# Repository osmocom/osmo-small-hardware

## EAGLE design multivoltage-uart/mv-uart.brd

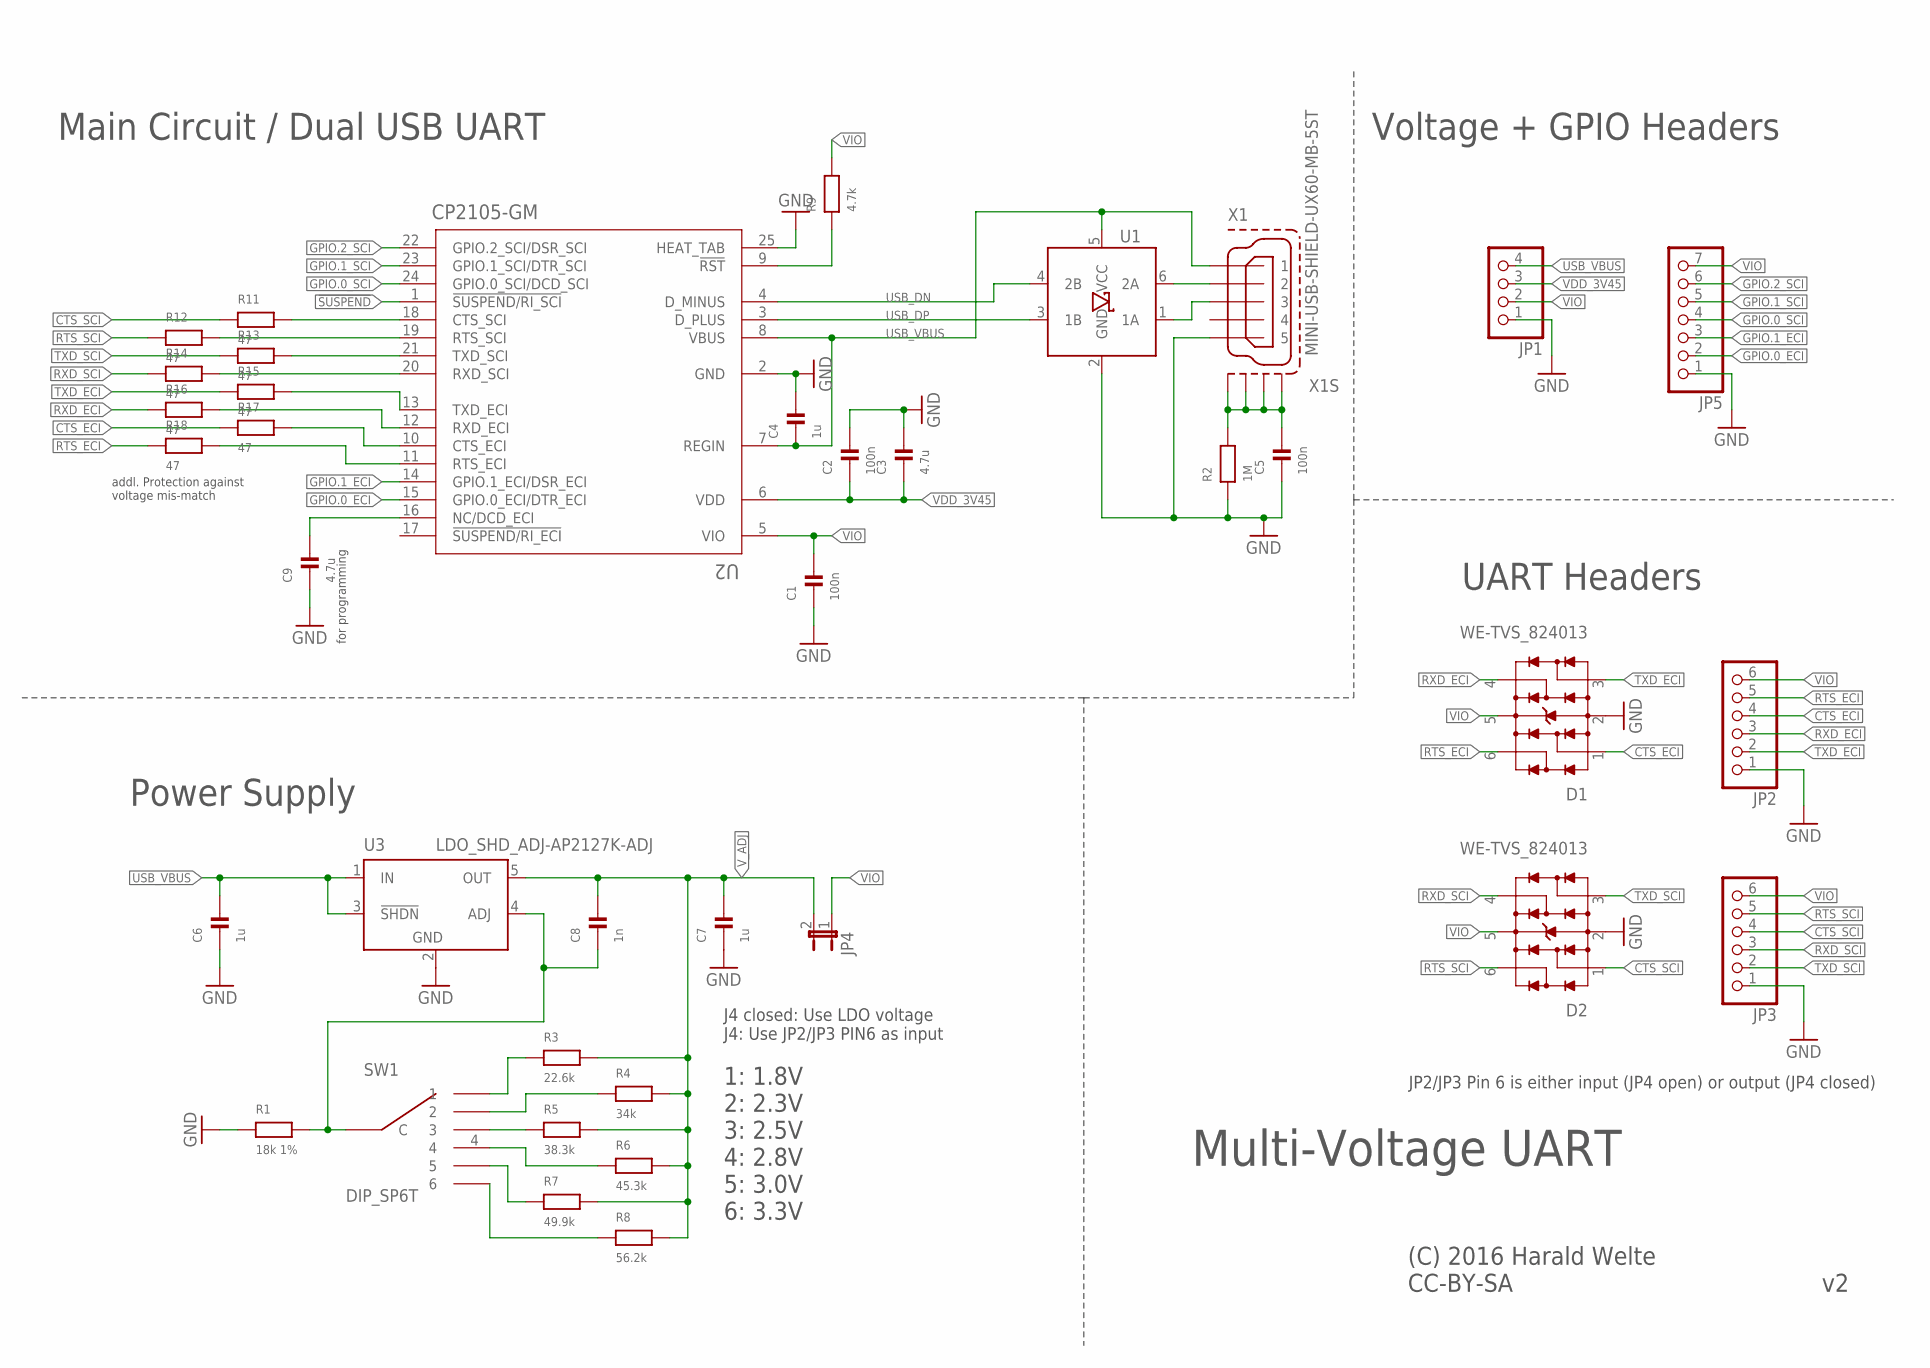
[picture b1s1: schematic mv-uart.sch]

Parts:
C1, C2, C5: 100n; _0603; MANUFACTURERPARTNUMBER GRM033R61C104KE84D
C3, C9: 4.7u; _0603; MANUFACTURERPARTNUMBER CL10A475KP8NNNC
C4, C6, C7: 1u; _0603; MANUFACTURERPARTNUMBER GRM188R61C105KA93J
C8: 1n; _0603; MANUFACTURERPARTNUMBER CL10B102KC8NNNC
D1, D2: WE-TVS_824013; WE-TVS_SOT23-6L; MANUFACTURERPARTNUMBER 824013
JP1: PINHD-1X4; 1X04; MANUFACTURERPARTNUMBER M20-9990445
JP2, JP3: PINHD-1X6/90; 1X06/90; MANUFACTURERPARTNUMBER M20-9960645
JP4: JP1E; JP1; MANUFACTURERPARTNUMBER UNKNOWN MANUFACTURER PART NUMBER
JP5: PINHD-1X7; 1X07; MANUFACTURERPARTNUMBER PRPC007SAAN-RC
R1: 18k 1%; _0603; MANUFACTURERPARTNUMBER RC0603FR-0718KL
R2: 1M; _0603; MANUFACTURERPARTNUMBER RC0603J105CS
R3: 22.6k; _0603; MANUFACTURERPARTNUMBER RC0603FR-0722K6L
R4: 34k; _0603; MANUFACTURERPARTNUMBER RC0603FR-0734KL
R5: 38.3k; _0603; MANUFACTURERPARTNUMBER RC0603FR-0738K3L
R6: 45.3k; _0603; MANUFACTURERPARTNUMBER RC0603FR-0745K3L
R7: 49.9k; _0603; MANUFACTURERPARTNUMBER RC0603FR-0749K9L
R8: 56.2k; _0603; MANUFACTURERPARTNUMBER RC0603FR-0756K2L
R9: 4.7k; _0603; MANUFACTURERPARTNUMBER RC0603JR-074K7L
R11, R12, R13, R14, R15, R16, R17, R18: 47; _0603; MANUFACTURERPARTNUMBER RC0603JR-0747RL
SW1: DIP_SP6T; MANUFACTURERPARTNUMBER SS-10-16SP-L-AE
U1: IP4234CZ6; TSOP-6; MANUFACTURERPARTNUMBER IP4234CZ6,125
U2: CP2105-GM; QFN24_4X4; MANUFACTURERPARTNUMBER CP2105-F01-GM
U3: LDO_SHD_ADJ-AP2127K-ADJ; SOT23L; MANUFACTURERPARTNUMBER AP2127K-ADJTRG1
X1: MINI-USB-SHIELD-UX60-MB-5ST; UX60-MB-5ST; MANUFACTURERPARTNUMBER UX60-MB-5ST

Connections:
!SUSPEND: U2.1 (!SUSPEND/RI_SCI)
CTS_ECI: D1.1, JP2.4, R17.1
CTS_SCI: D2.1, JP3.4, R11.1
GND: C1.1, C2.2, C3.2, C4.2, C5.1, C6.1, C7.1, C9.1, D1.2 (GND), D2.2 (GND), JP1.1, JP2.1, JP3.1, JP5.1, R1.1, R2.1, U1.2 (GND), U2.2 (GND), U2.25 (HEAT_TAB), U3.2 (GND), X1.5
GPIO.0_ECI: JP5.2, U2.15 (GPIO.0_ECI/DTR_ECI)
GPIO.0_SCI: JP5.4, U2.24 (GPIO.0_SCI/DCD_SCI)
GPIO.1_ECI: JP5.3, U2.14 (GPIO.1_ECI/DSR_ECI)
GPIO.1_SCI: JP5.5, U2.23 (GPIO.1_SCI/DTR_SCI)
GPIO.2_SCI: JP5.6, U2.22 (GPIO.2_SCI/DSR_SCI)
unnamed: R3.1, SW1.1
unnamed: R4.1, SW1.2
unnamed: R5.1, SW1.3
unnamed: R6.1, SW1.4
unnamed: C5.2, R2.2, X1.M1 (S1), X1.M2 (S2), X1.M3 (S3), X1.M4 (S4)
unnamed: R7.1, SW1.5
unnamed: R8.1, SW1.6
unnamed: R9.1, U2.9 (!RST)
unnamed: C9.2, U2.16 (NC/DCD_ECI)
unnamed: R11.2, U2.18 (CTS_SCI)
unnamed: R12.2, U2.19 (RTS_SCI)
unnamed: R13.2, U2.21 (TXD_SCI)
unnamed: R14.2, U2.20 (RXD_SCI)
unnamed: R15.2, U2.13 (TXD_ECI)
unnamed: C8.1, R1.2, SW1.C, U3.4 (ADJ)
unnamed: R16.2, U2.12 (RXD_ECI)
unnamed: R17.2, U2.10 (CTS_ECI)
unnamed: R18.2, U2.11 (RTS_ECI)
RTS_ECI: D1.6 (4), JP2.5, R18.1
RTS_SCI: D2.6 (4), JP3.5, R12.1
RXD_ECI: D1.4 (3), JP2.3, R16.1
RXD_SCI: D2.4 (3), JP3.3, R14.1
TXD_ECI: D1.3 (2), JP2.2, R15.1
TXD_SCI: D2.3 (2), JP3.2, R13.1
USB_DN: U1.4 (2B), U2.4 (D_MINUS)
USB_DP: U1.3 (1B), U2.3 (D_PLUS)
USB_VBUS: C4.1, C6.2, JP1.4, U1.5 (VCC), U2.7 (REGIN), U2.8 (VBUS), U3.1 (IN), U3.3 (!SHDN), X1.1
VDD_3V45: C2.1, C3.1, JP1.3, U2.6 (VDD)
VIO: C1.2, D1.5 (VDD), D2.5 (VDD), JP1.2, JP2.6, JP3.6, JP4.1, JP5.7, R9.2, U2.5 (VIO)
V_ADJ: C7.2, C8.2, JP4.2, R3.2, R4.2, R5.2, R6.2, R7.2, R8.2, U3.5 (OUT)
_USB_DN: U1.6 (2A), X1.2
_USB_DP: U1.1 (1A), X1.3

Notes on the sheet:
Main Circuit / Dual USB UART
Power Supply
Voltage + GPIO Headers
UART Headers
Multi-Voltage UART
(C) 2016 Harald Welte CC-BY-SA
J4 closed: Use LDO voltage J4: Use JP2/JP3 PIN6 as input
JP2/JP3 Pin 6 is either input (JP4 open) or output (JP4 closed)
addl. Protection against voltage mis-match
for programming
1: 1.8V 2: 2.3V 3: 2.5V 4: 2.8V 5: 3.0V 6: 3.3V

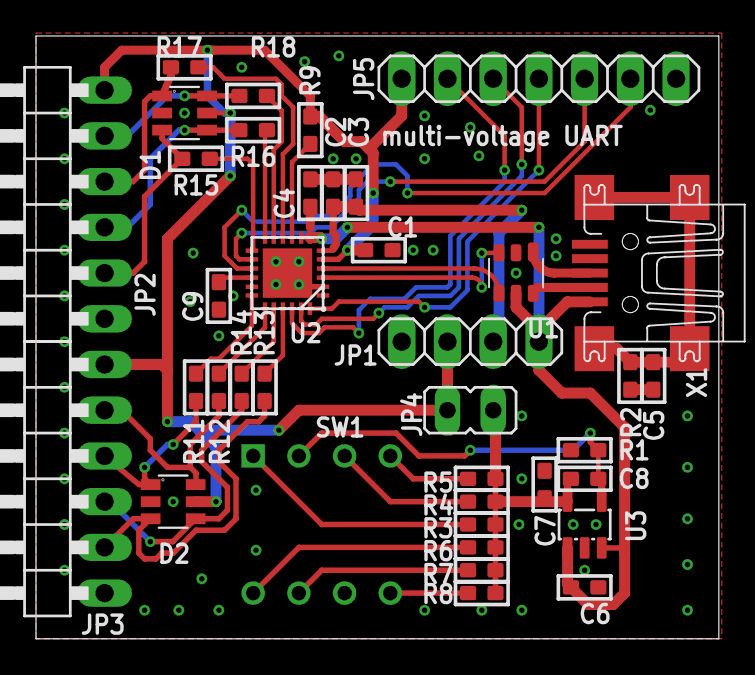
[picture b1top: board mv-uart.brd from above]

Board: 2 copper layers, 37.9 x 33.5 mm, 38 parts (0 on the bottom side), 40 nets.

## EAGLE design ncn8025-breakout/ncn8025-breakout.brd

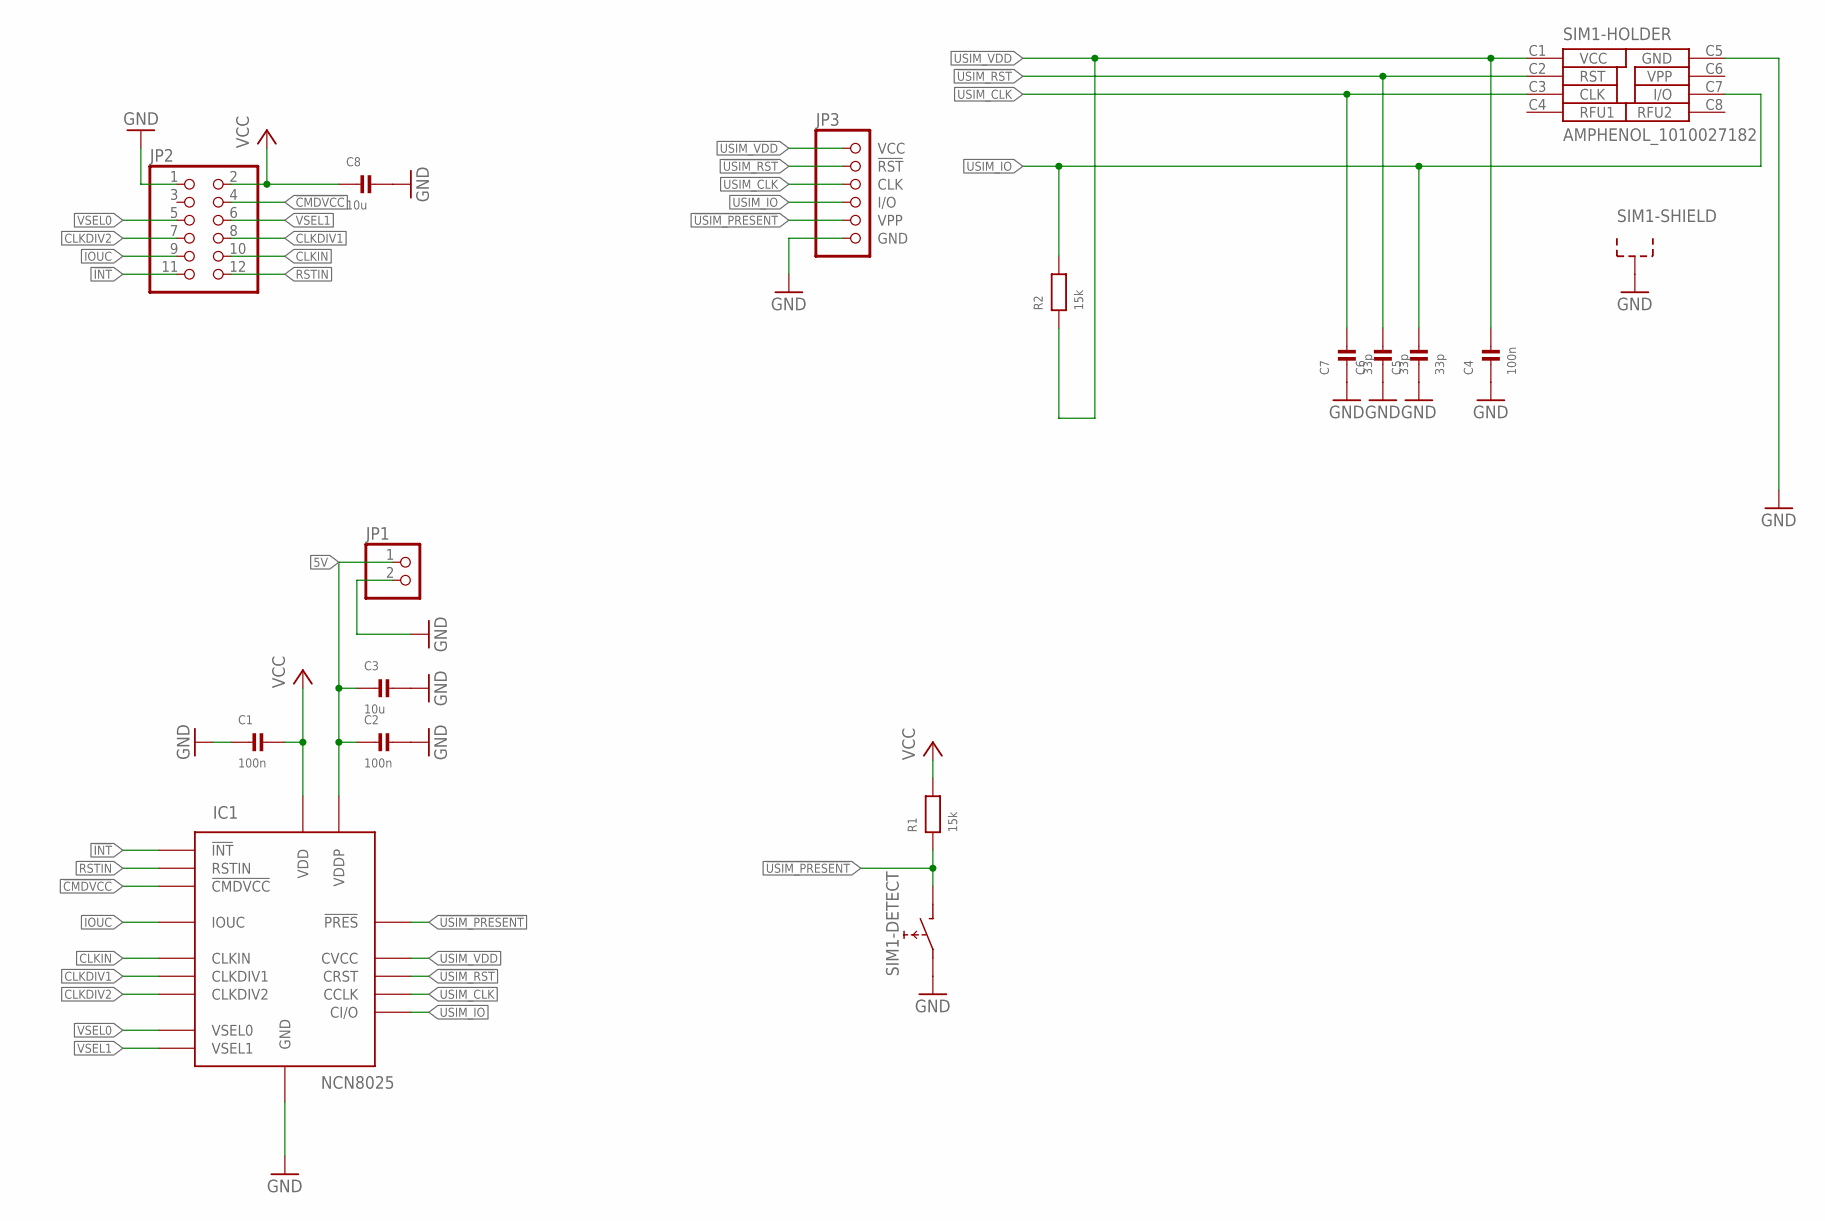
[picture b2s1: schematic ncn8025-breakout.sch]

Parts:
C1, C2, C4: 100n; _0603
C3, C8: 10u; _0603
C5, C6, C7: 33p; _0603
IC1: NCN8025; QFN16_3X3
JP1: PINHD-1X2; 1X02
JP2: PINHD-2X6; 2X06
JP3: PINHD-1X6; 1X06
R1, R2: 15k; _0603
SIM1: AMPHENOL_1010027182; SIM-AMPHENOL

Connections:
5V: C2.1, C3.1, IC1.2 (VDDP), JP1.1
!CMDVCC: IC1.8 (!CMDVCC), JP2.4
!INT: IC1.11 (!INT), JP2.11
!USIM_PRESENT: IC1.3 (!PRES), JP3.5 (VPP), R1.1, SIM1.SW2 (1)
!USIM_RST: C6.2, IC1.6 (CRST), JP3.2 (!RST), SIM1.C2 (RST)
CLKDIV1: IC1.14 (CLKDIV1), JP2.8
CLKDIV2: IC1.15 (CLKDIV2), JP2.7
CLKIN: IC1.12 (CLKIN), JP2.10
GND: C1.1, C2.2, C3.2, C4.1, C5.1, C6.1, C7.1, C8.2, IC1.EXPPAD (GND), JP1.2, JP2.1, JP3.6 (GND), SIM1.@2 (SHLD), SIM1.@3 (SHLD), SIM1.C5 (GND), SIM1.SW1 (0)
IOUC: IC1.13 (IOUC), JP2.9
RSTIN: IC1.9 (RSTIN), JP2.12
USIM_CLK: C7.2, IC1.5 (CCLK), JP3.3 (CLK), SIM1.C3 (CLK)
USIM_IO: C5.2, IC1.4 (CI/O), JP3.4 (I/O), R2.2, SIM1.C7 (I/O)
USIM_VDD: C4.2, IC1.7 (CVCC), JP3.1 (VCC), R2.1, SIM1.C1 (VCC)
VCC: C1.2, C8.1, IC1.10 (VDD), JP2.2, R1.2
VPP: SIM1.C6 (VPP)
VSEL0: IC1.1 (VSEL0), JP2.5
VSEL1: IC1.16 (VSEL1), JP2.6

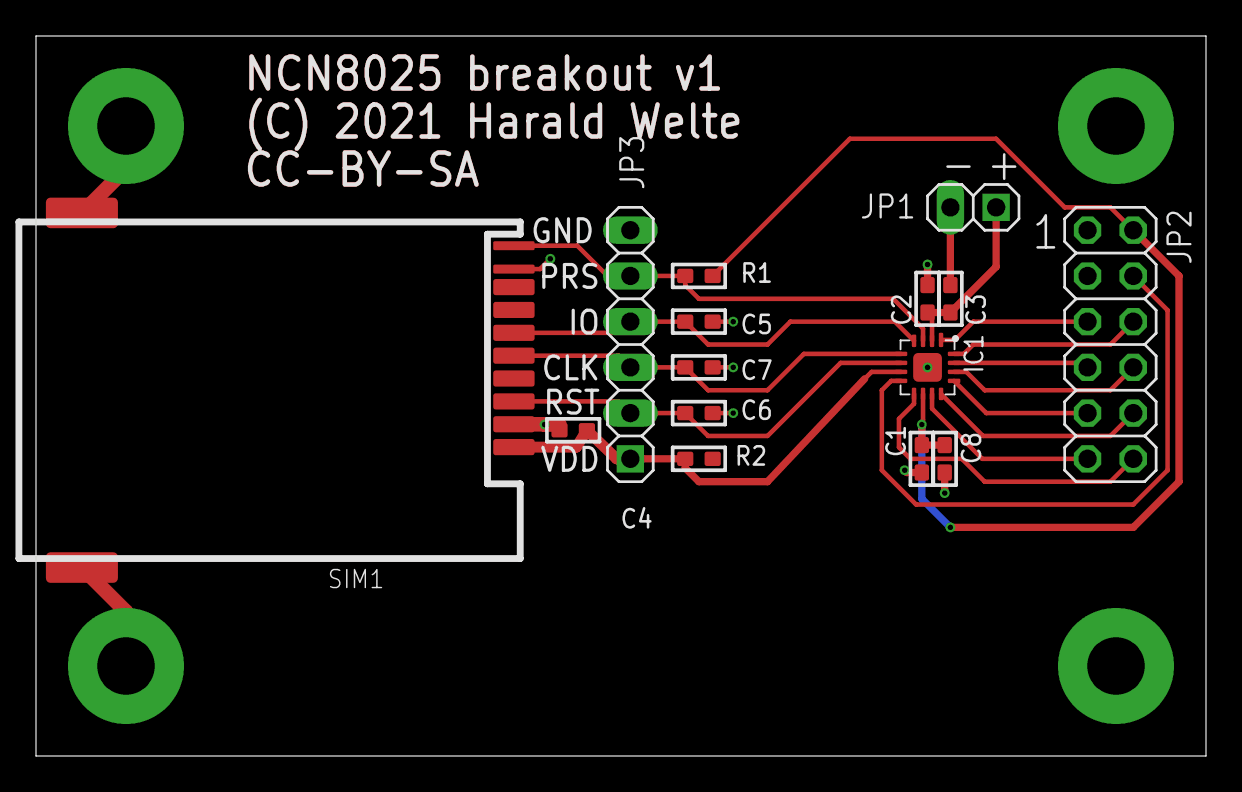
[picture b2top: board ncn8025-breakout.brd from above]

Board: 2 copper layers, 65.0 x 40.0 mm, 15 parts (0 on the bottom side), 17 nets.

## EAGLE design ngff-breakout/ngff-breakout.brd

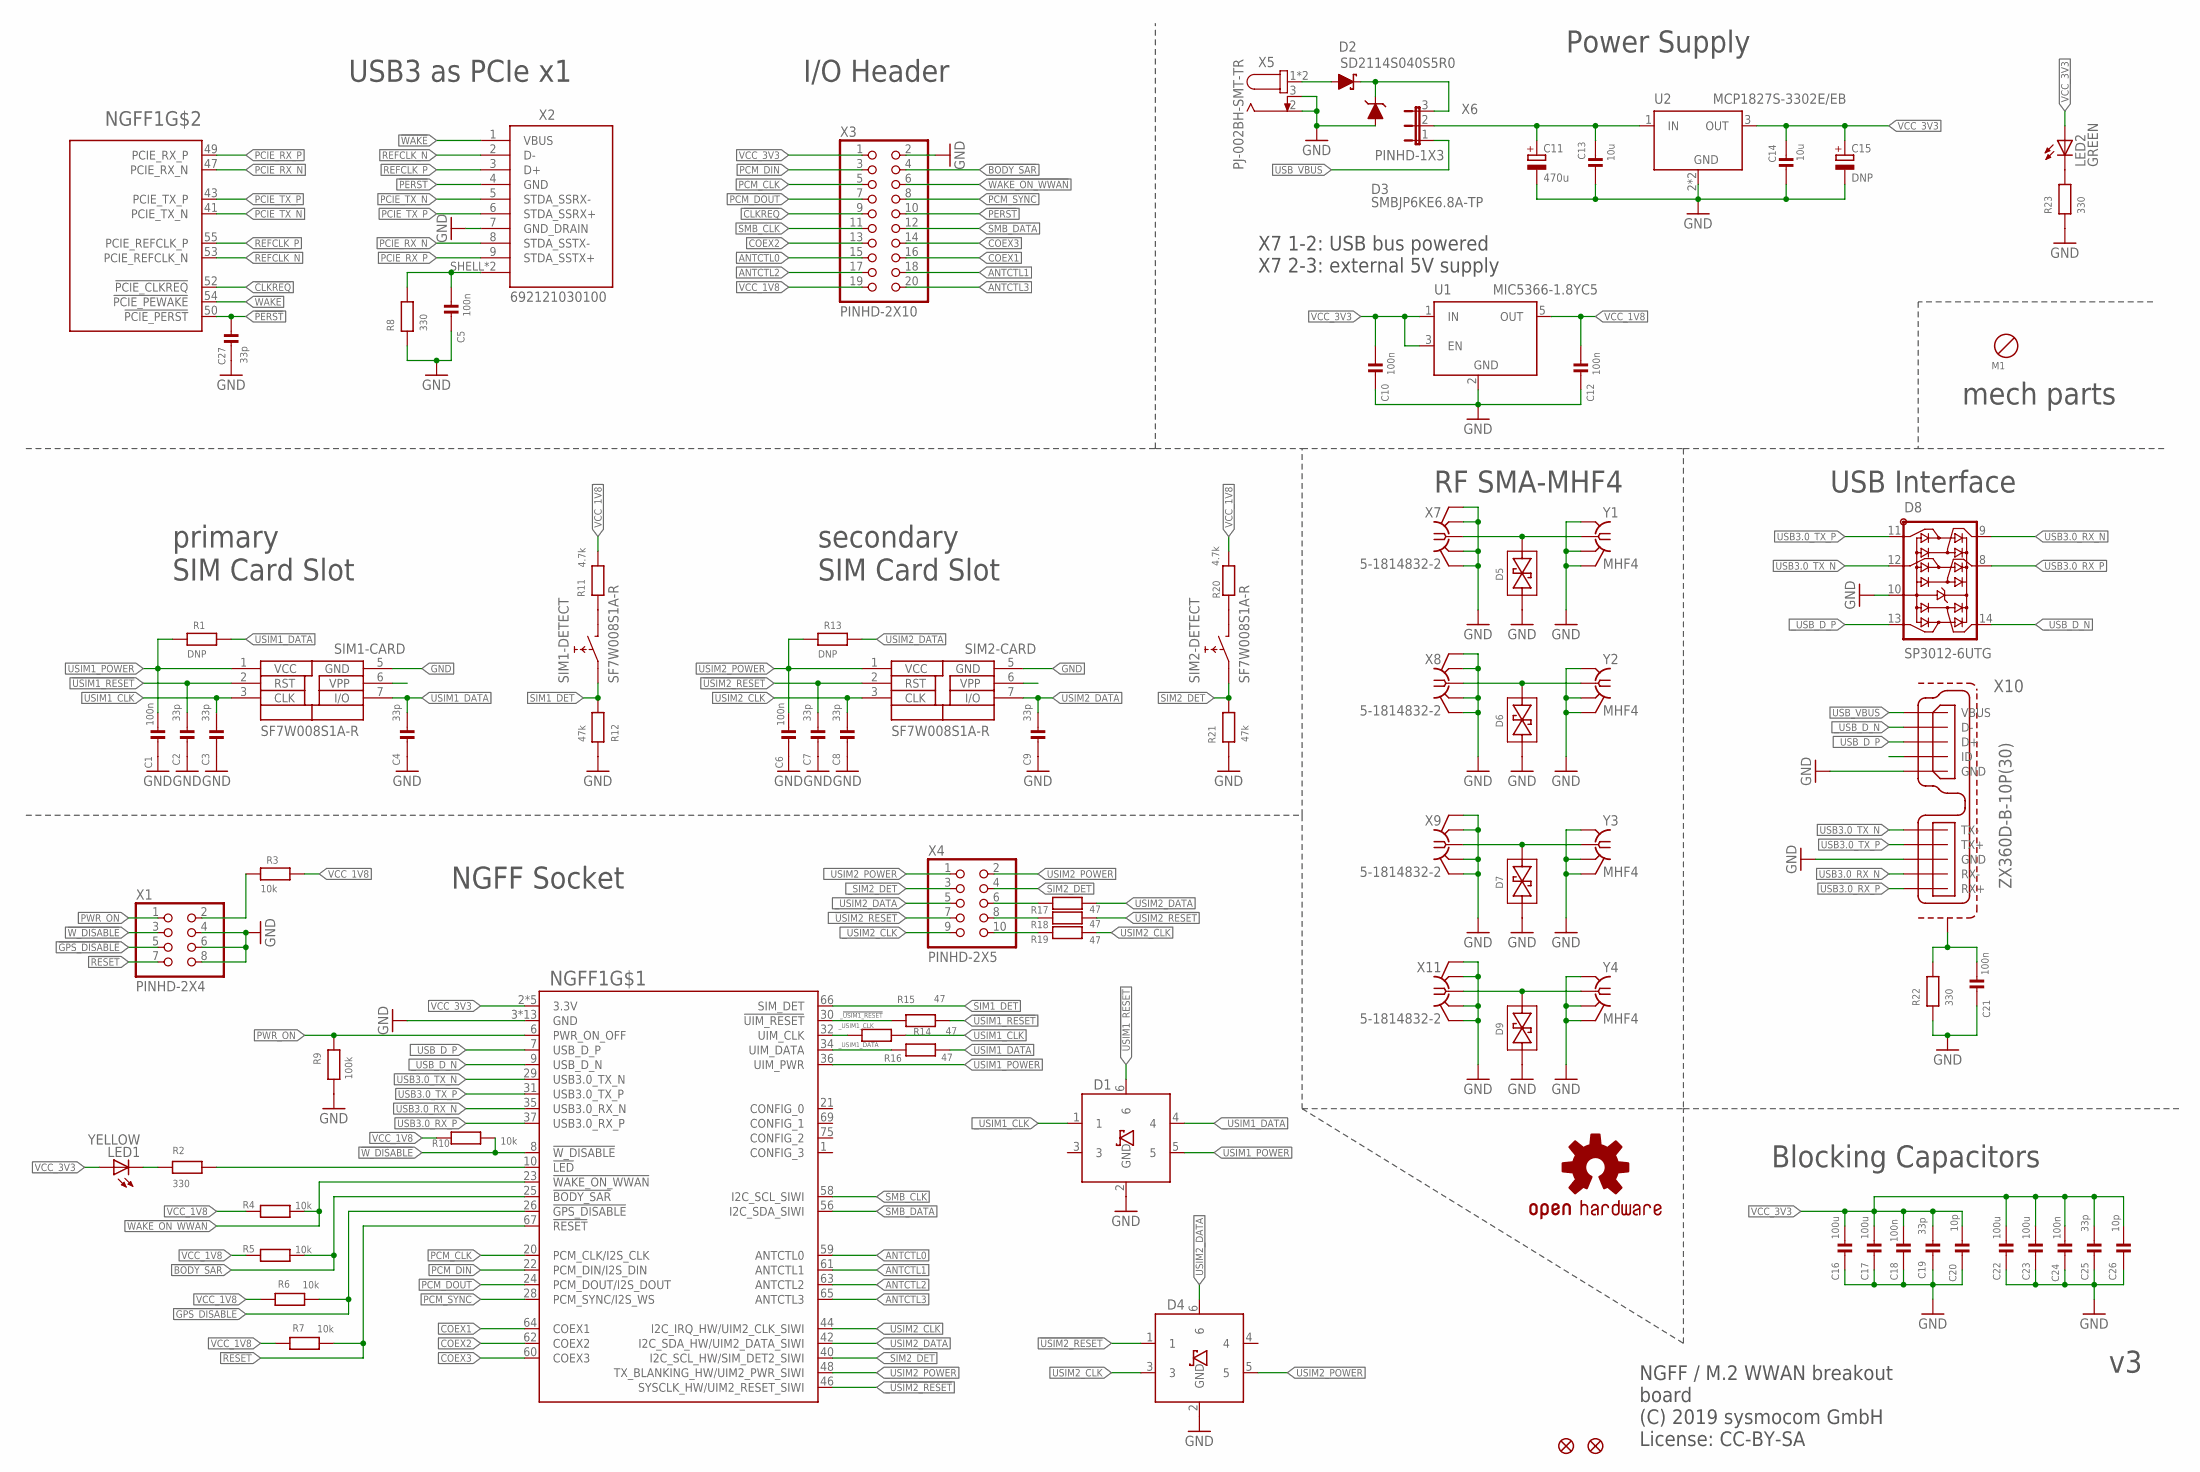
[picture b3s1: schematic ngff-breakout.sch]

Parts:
C1, C5, C6, C10, C12, C18, C21, C24: 100n; _0603; MANUFACTURERPARTNUMBER CL10B104KO8NNNC
C2, C3, C4, C7, C8, C9, C19, C25, C27: 33p; _0402; MANUFACTURERPARTNUMBER CL05C330JB5NNNC
C11: 470u; UD-8X10_NICHICON; MANUFACTURERPARTNUMBER UUR0J471MNL1GS
C13, C14: 10u; _0805; MANUFACTURERPARTNUMBER CL21A106KOQNNNG
C15: DNP; SMC_E; MANUFACTURERPARTNUMBER UNKNOWN MANUFACTURER PART NUMBER
C16, C17, C22, C23: 100u; 1206; MANUFACTURERPARTNUMBER GRM31CR60J107ME39K
C20, C26: 10p; _0603; MANUFACTURERPARTNUMBER C0603C100J5GACTU
D1, D4: PESD5V0UBV; SOT666; MANUFACTURERPARTNUMBER PESD5V0U5BV,115
D2: SD2114S040S5R0; SMBDIODE; MANUFACTURERPARTNUMBER YPE HTML PUBLIC
D3: SMBJP6KE6.8A-TP; SMBDIODE; MANUFACTURERPARTNUMBER SMBJP6KE6.8A-TP
D5, D6, D7, D9: GG040205170N2P; _0402; MANUFACTURERPARTNUMBER GG040205170N2P
D8: SP3012-6UTG; UDFN-14; MANUFACTURERPARTNUMBER SP3012-06UTG
JP1, JP2: FIDUCIALUFIDUCIAL; MICRO-FIDUCIAL; MANUFACTURERPARTNUMBER UNKNOWN MANUFACTURER PART NUMBER
LED1: YELLOW; CHIP-LED0603; MANUFACTURERPARTNUMBER UNKNOWN MANUFACTURER PART NUMBER
LED2: GREEN; CHIP-LED0603; MANUFACTURERPARTNUMBER UNKNOWN MANUFACTURER PART NUMBER
LOGO1: OSHW-LOGOL-COPPER; OSHW-LOGO-L_COPPER; MANUFACTURERPARTNUMBER UNKNOWN MANUFACTURER PART NUMBER
NGFF1: NGFF_B-NSOL; NGFF_3042_3052_NSOL; MANUFACTURERPARTNUMBER 2199230-3
R1, R13: DNP; _0603; MANUFACTURERPARTNUMBER YPE HTML PUBLIC
R2, R8, R22, R23: 330; _0603; MANUFACTURERPARTNUMBER RC0603JR-07330RL
R3, R4, R5, R7, R10: 10k; _0603; MANUFACTURERPARTNUMBER YPE HTML PUBLIC
R6: 10k; _0603; MANUFACTURERPARTNUMBER RMCF0603FT10K0
R9: 100k; _0603; MANUFACTURERPARTNUMBER CRCW0603100KFKEA
R11, R20: 4.7k; _0603; MANUFACTURERPARTNUMBER RC0603JR-074K7L
R12, R21: 47k; _0603; MANUFACTURERPARTNUMBER RMCF0603FT47K0
R14, R15, R16, R17, R18, R19: 47; _0402; MANUFACTURERPARTNUMBER CRGCQ0402F47R
SIM1, SIM2: SF7W008S1A-R; SF7W008S1A-RESTR; MANUFACTURERPARTNUMBER SF7W008S1AR900
U1: MIC5366-1.8YC5; SC70-5; MANUFACTURERPARTNUMBER MIC5366-1.8YC5-TR
U2: MCP1827S-3302E/EB; TO263; MANUFACTURERPARTNUMBER YPE HTML PUBLIC
X1: PINHD-2X4; 2X04; MANUFACTURERPARTNUMBER PH2-08-UA
X2: 692121030100; MANUFACTURERPARTNUMBER 692121030100
X3: PINHD-2X10; 2X10; MANUFACTURERPARTNUMBER PH2-20-UA
X4: PINHD-2X5; 2X05; MANUFACTURERPARTNUMBER PH2-10-UA
X5: PJ-002BH-SMT-TR; 694108106102; MANUFACTURERPARTNUMBER PJ-002BH-SMT-TR
X6: PINHD-1X3; JP2; MANUFACTURERPARTNUMBER PH1-03-UA
X7, X8, X9, X11: 5-1814832-2; SMA-F-S-TH; MANUFACTURERPARTNUMBER 5-1814832-2
X10: ZX360D-B-10P(30); ZX360D-B; MANUFACTURERPARTNUMBER ZX360D-B-10P(30)
Y1, Y2, Y3, Y4: MHF4; MURATA_HSC; MANUFACTURERPARTNUMBER MM4829-2702RA4

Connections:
!BODY_SAR: NGFF1.25 (!BODY_SAR), R5.1, X3.4
!CLKREQ: NGFF1.52 (!PCIE_CLKREQ), X3.9
!GPS_DISABLE: NGFF1.26 (!GPS_DISABLE), R6.1, X1.5
!PERST: C27.1, NGFF1.50 (!PCIE_PERST), X2.4 (GND), X3.10
!RESET: NGFF1.67 (!RESET), R7.1, X1.7
!USIM1_RESET: C2.1, R15.2, SIM1.2 (RST)
!USIM2_RESET: C7.1, D4.1, R18.2, SIM2.2 (RST)
!WAKE: NGFF1.54 (!PCIE_PEWAKE), X2.1 (VBUS)
!WAKE_ON_WWAN: NGFF1.23 (!WAKE_ON_WWAN), R4.1, X3.6
!W_DISABLE: NGFF1.8 (!W_DISABLE), R10.1, X1.3
ANTCTL0: NGFF1.59 (ANTCTL0), X3.15
ANTCTL1: NGFF1.61 (ANTCTL1), X3.18
ANTCTL2: NGFF1.63 (ANTCTL2), X3.17
ANTCTL3: NGFF1.65 (ANTCTL3), X3.20
COEX1: NGFF1.64 (COEX1), X3.16
COEX2: NGFF1.62 (COEX2), X3.13
COEX3: NGFF1.60 (COEX3), X3.14
GND: C1.1, C2.2, C3.2, C4.2, C5.1, C6.1, C7.2, C8.2, C9.2, C10.1, C11.-, C12.1, C13.1, C14.1, C15.-, C16.1, C17.1, C18.1, C19.2, C20.2, C21.1, C22.1, C23.1, C24.1, C25.2, C26.2, C27.2, D1.2 (GND), D3.A, D4.2 (GND), D5.1, D6.1, D7.1, D8.10 (GND), D9.1, NGFF1.3 (GND), NGFF1.5 (GND), NGFF1.11 (GND), NGFF1.27 (GND), NGFF1.33 (GND), NGFF1.39 (GND), NGFF1.45 (GND), NGFF1.51 (GND), NGFF1.57 (GND), NGFF1.71 (GND), NGFF1.73 (GND), NGFF1.P$1 (GND), NGFF1.P$2 (GND), R8.1, R9.1, R12.1, R21.1, R22.1, R23.1, SIM1.5 (GND), SIM2.5 (GND), U1.2 (GND), U2.2 (GND), U2.4 (GND), X1.4, X1.6, X1.8, X2.7 (GND_DRAIN), X3.2, X5.2, X5.3, X7.G1 (GND), X7.G2 (GND), X7.G3 (GND), X7.G4 (GND), X8.G1 (GND), X8.G2 (GND), X8.G3 (GND), X8.G4 (GND), X9.G1 (GND), X9.G2 (GND), X9.G3 (GND), X9.G4 (GND), X10.5 (GND), X10.8 (GND), X11.G1 (GND), X11.G2 (GND), X11.G3 (GND), X11.G4 (GND), Y1.P$1 (GND), Y1.P$2 (GND), Y1.P$4 (GND), Y2.P$1 (GND), Y2.P$2 (GND), Y2.P$4 (GND), Y3.P$1 (GND), Y3.P$2 (GND), Y3.P$4 (GND), Y4.P$1 (GND), Y4.P$2 (GND), Y4.P$4 (GND)
LDO_IN: C11.+, C13.2, U2.1 (IN), X6.2
unnamed: LED2.C, R23.2
unnamed: LED1.C, R2.1
unnamed: D2.A, X5.1, X5.1-1 (1)
unnamed: C5.2, R8.2, X2.SHELL (SHIELD), X2.SHELL1 (SHIELD)
unnamed: NGFF1.10 (!LED), R2.2
unnamed: D7.2, X9.C (1), Y3.1
unnamed: R11.2, SIM1.82 (1)
unnamed: C21.2, R22.2, X10.S1, X10.S2 (S1), X10.S3 (S1), X10.S4 (S1), X10.S5 (S1), X10.S6 (S1), X10.S7 (S1), X10.S8 (S1)
unnamed: R20.2, SIM2.82 (1)
unnamed: D2.C, D3.C, X6.3
unnamed: D5.2, X7.C (1), Y1.1
unnamed: D6.2, X8.C (1), Y2.1
unnamed: R17.1, X4.6
unnamed: R18.1, X4.8
unnamed: R3.1, X1.2
unnamed: R19.1, X4.10
unnamed: D9.2, X11.C (1), Y4.1
PCIE_RX_N: NGFF1.47 (PCIE_RX_N), X2.8 (STDA_SSTX-)
PCIE_RX_P: NGFF1.49 (PCIE_RX_P), X2.9 (STDA_SSTX+)
PCIE_TX_N: NGFF1.41 (PCIE_TX_N), X2.5 (STDA_SSRX-)
PCIE_TX_P: NGFF1.43 (PCIE_TX_P), X2.6 (STDA_SSRX+)
PCM_CLK: NGFF1.20 (PCM_CLK/I2S_CLK), X3.5
PCM_DIN: NGFF1.22 (PCM_DIN/I2S_DIN), X3.3
PCM_DOUT: NGFF1.24 (PCM_DOUT/I2S_DOUT), X3.7
PCM_SYNC: NGFF1.28 (PCM_SYNC/I2S_WS), X3.8
PWR_ON: NGFF1.6 (PWR_ON_OFF), R9.2, X1.1
REFCLK_N: NGFF1.53 (PCIE_REFCLK_N), X2.2 (D-)
REFCLK_P: NGFF1.55 (PCIE_REFCLK_P), X2.3 (D+)
SIM1_DET: NGFF1.66 (SIM_DET), R12.2, SIM1.81 (0)
SIM2_DET: R21.2, SIM2.81 (0), X4.4
SMB_CLK: NGFF1.58 (I2C_SCL_SIWI), X3.11
SMB_DATA: NGFF1.56 (I2C_SDA_SIWI), X3.12
USB3.0_RX_N: D8.9 (7), NGFF1.35 (USB3.0_RX_N), X10.9 (RX-)
USB3.0_RX_P: D8.8 (6), NGFF1.37 (USB3.0_RX_P), X10.10 (RX+)
USB3.0_TX_N: D8.12 (2), NGFF1.29 (USB3.0_TX_N), X10.6 (TX-)
USB3.0_TX_P: D8.11 (1), NGFF1.31 (USB3.0_TX_P), X10.7 (TX+)
USB_VBUS: X6.1, X10.1 (VBUS)
USIM1_CLK: C3.1, R14.2, SIM1.3 (CLK)
USIM1_DATA: C4.1, R1.2, R16.2, SIM1.7 (I/O)
USIM1_POWER: C1.2, D1.5, NGFF1.36 (UIM_PWR), R1.1, SIM1.1 (VCC)
USIM2_CLK: C8.1, D4.3, R19.2, SIM2.3 (CLK)
USIM2_DATA: C9.1, D4.6, R13.2, R17.2, SIM2.7 (I/O)
USIM2_POWER: C6.2, D4.5, R13.1, SIM2.1 (VCC), X4.2
VCC_1V8: C12.2, R3.2, R4.2, R5.2, R6.2, R7.2, R10.2, R11.1, R20.1, U1.5 (OUT), X3.19
VCC_3V3: C10.2, C14.2, C15.+, C16.2, C17.2, C18.2, C19.1, C20.1, C22.2, C23.2, C24.2, C25.1, C26.1, LED1.A, LED2.A, NGFF1.2 (3.3V), NGFF1.4 (3.3V), NGFF1.70 (3.3V), NGFF1.72 (3.3V), NGFF1.74 (3.3V), U1.1 (IN), U1.3 (EN), U2.3 (OUT), X3.1
_!USIM1_RESET: D1.6, NGFF1.30 (!UIM_RESET), R15.1
_!USIM2_RESET: NGFF1.46 (SYSCLK_HW/UIM2_RESET_SIWI), X4.7
_SIM2_DET: NGFF1.40 (I2C_SCL_HW/SIM_DET2_SIWI), X4.3
_USB_D_N: D8.14 (5), NGFF1.9 (USB_D_N), X10.2 (D-)
_USB_D_P: D8.13 (4), NGFF1.7 (USB_D_P), X10.3 (D+)
_USIM1_CLK: D1.1, NGFF1.32 (UIM_CLK), R14.1
_USIM1_DATA: D1.4, NGFF1.34 (UIM_DATA), R16.1
_USIM2_CLK: NGFF1.44 (I2C_IRQ_HW/UIM2_CLK_SIWI), X4.9
_USIM2_DATA: NGFF1.42 (I2C_SDA_HW/UIM2_DATA_SIWI), X4.5
_USIM2_POWER: NGFF1.48 (TX_BLANKING_HW/UIM2_PWR_SIWI), X4.1

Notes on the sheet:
NGFF / M.2 WWAN breakout board (C) 2019 sysmocom GmbH License: CC-BY-SA
I/O Header
primary SIM Card Slot
NGFF Socket
Power Supply
Blocking Capacitors
USB Interface
X7 1-2: USB bus powered X7 2-3: external 5V supply
RF SMA-MHF4
mech parts
USB3 as PCIe x1
secondary SIM Card Slot

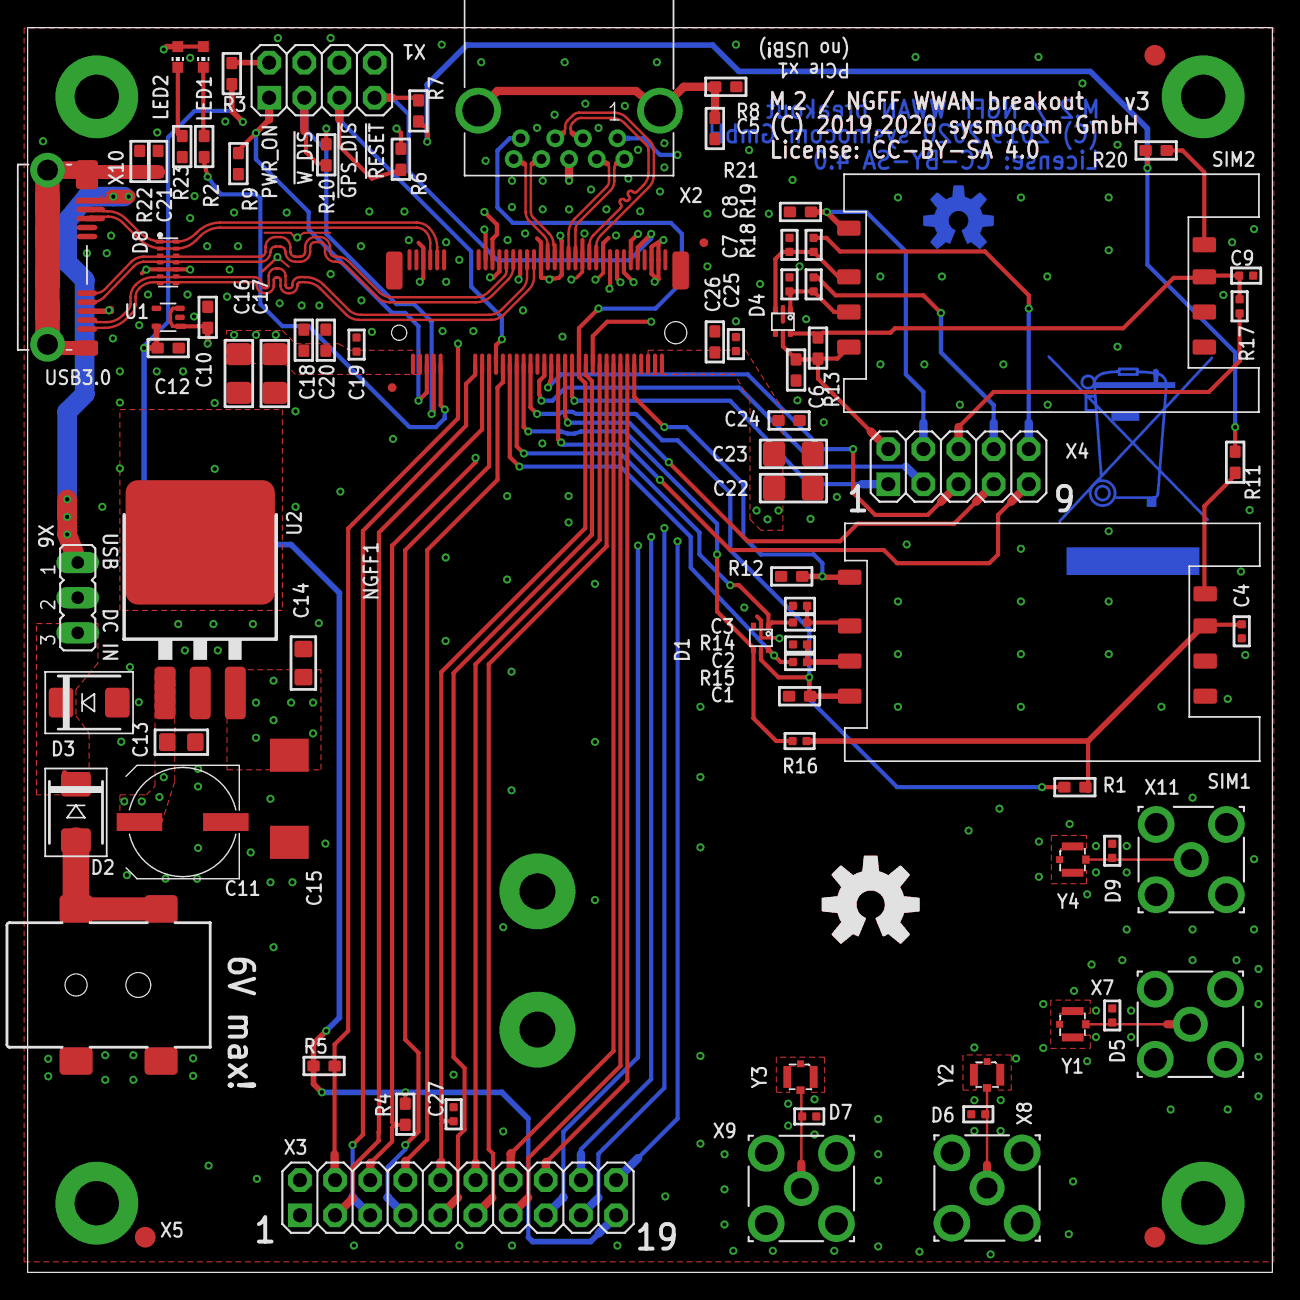
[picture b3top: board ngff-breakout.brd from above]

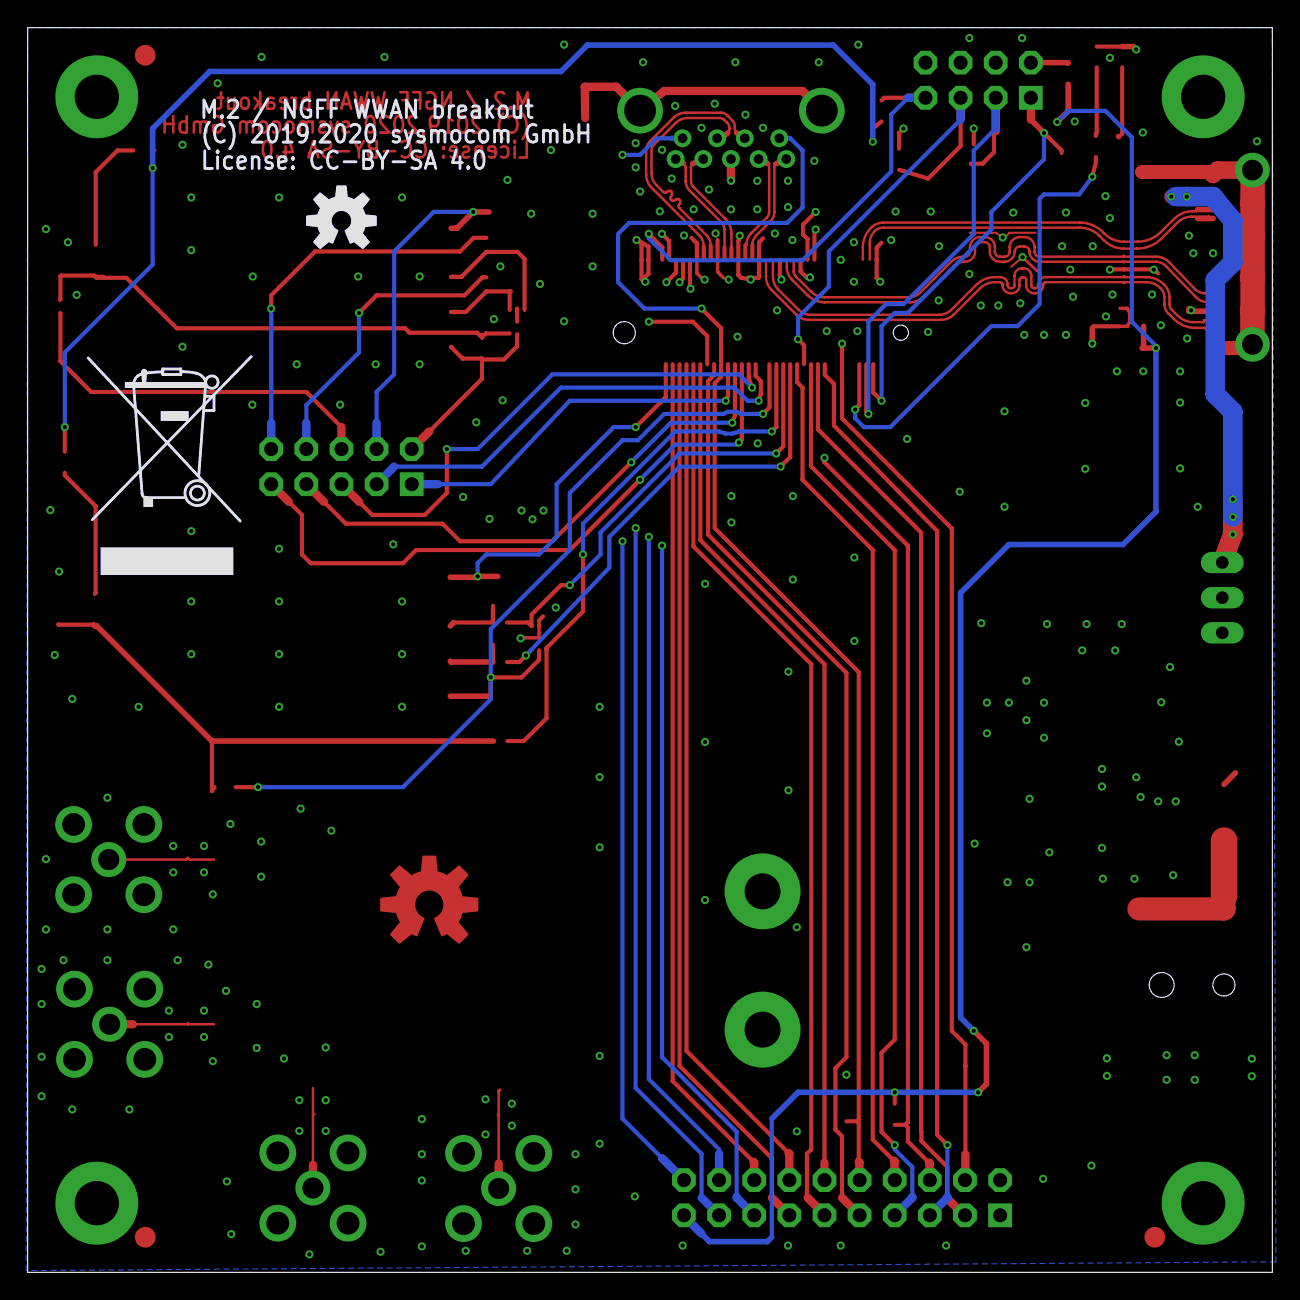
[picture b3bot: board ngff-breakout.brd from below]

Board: 4 copper layers, 90.0 x 90.0 mm, 92 parts (4 on the bottom side), 74 nets.

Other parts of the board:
FID1, FID2, FID3: VISION_REF15
U$1: WEEE_BIN_TOP
U$2: WEEE_BIN
U$3: OSHW-LOGO-M_COPPER
U$4: OSHW-LOGO-M
U$7: OSHW-LOGO-L

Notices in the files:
ncn8025-breakout/ncn8025-breakout.brd:
(C) 2021 Harald Welte
CC-BY-SA
ngff-breakout/ngff-breakout.brd:
(C) 2019,2020 sysmocom GmbH
License: CC-BY-SA 4.0
osmo-lea6t-gps/eagle/ublox-lea6-test.brd:
(c) 2012 Munaut
parts and their libraries:
Wuerth_Elektronik_eiSos_V6_20140807: Copyright: Würth Elektronik
SparkFun: Licensing: CC v3.0 Share-Alike You are welcome to use this library for commercial purposes.
SparkFun-Aesthetics: Licensing: Creative Commons ShareAlike 4.0 International - https://creativecommons.org/licenses/by-sa/4.0
